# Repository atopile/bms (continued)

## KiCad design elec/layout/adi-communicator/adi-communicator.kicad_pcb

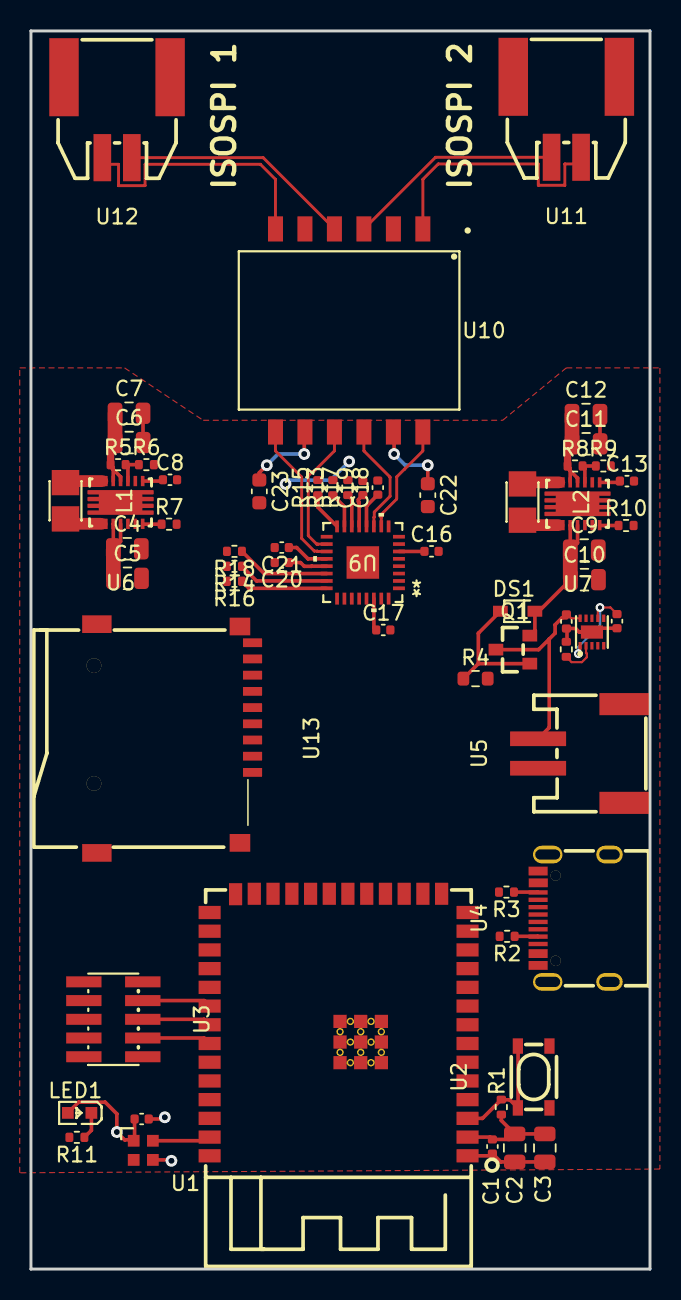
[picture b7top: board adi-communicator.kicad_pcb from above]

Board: 4 copper layers, 42.0 x 84.0 mm, 61 parts (0 on the bottom side), 53 nets.

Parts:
C1, C8, C13, C16, C17, C18, C19, C20, C21, C24: 16V 100nF X7R ±10% 0402 Multilayer Ceramic Capaci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; C0402
C2, C3, C4, C5, C6, C7, C9, C10, C11, C12: 25V 10uF X5R ±10% 0805 Multilayer Ceramic Capacit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; C0805
C14, C15: 25V 1uF X5R ±10% 0402 Multilayer Ceramic Capacito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; C0402
C22, C23: 50V 10nF X7R ±10% 0603 Multilayer Ceramic Capacit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; C0603
DS1: SOD-323_L1.8-W1.3-LS2.5-RD
L1, L2: IND-SMD_L2.5-W2.0_WPN252012H
LED1: LED0603-RD
Q1: SOT-23_L2.9-W1.3-P1.90-LS2.4-BR
R1: 62.5mW Thick Film Resistors 50V ±100ppm/℃ ±1% 10k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; R0402
R2, R3: 62.5mW Thick Film Resistors 50V ±100ppm/℃ ±1% 4.7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; R0402
R4: 100mW Thick Film Resistors 75V ±100ppm/℃ ±1% 10kΩ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; R0603
R5: 62.5mW Thick Film Resistors 50V ±100ppm/℃ ±1% 25.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; R0402
R6: 62.5mW Thick Film Resistors ±100ppm/℃ ±1% 2.8kΩ 0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; R0402
R7, R10: 62.5mW Thick Film Resistors 50V ±100ppm/℃ ±1% 1MΩ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; R0402
R8: 62.5mW Thick Film Resistors 50V ±100ppm/℃ ±1% 23.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; R0402
R9: 62.5mW Thick Film Resistors 50V ±100ppm/℃ ±1% 4.3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; R0402
R11: 62.5mW Thick Film Resistors 50V ±100ppm/℃ ±1% 330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; R0402
R12: 62.5mW Thick Film Resistors 75V ±1% ±100ppm/℃ 576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; R0402
R13, R14, R15, R16, R17, R18: 0Ω; R0402
U1: WIRELM-SMD_ESP32-S3-WROOM-1
U2: KEY-SMD_4P-L4.2-W3.2-P2.20-LS4.6
U3: HDR-SMD_10P-P1.27-V-M-R2-C5-LS5.3
U4: USB-C-SMD_KH-TYPE-C-16P
U5: CONN-SMD_P2.00_S2B-PH-SM4-TB-LF-SN
U6, U7: VSON-14_L4.0-W3.0-P0.50-BL-EP_TI_DSJ
U8: WSON-10_L2.0-W2.0-P0.40-BL-EP
U9: 05-08-7057_ADI
U10: SMD-12_L14.8-W11.7-P2.00-LS14.7
U11, U12: CONN-SMD_2P-P2.00_MOLEX_5023520201
U13: TF-SMD_TF-01A
U14: LED-SMD_4P-L2.0-W2.0-BR

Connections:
_3v3_reg.feedback_div-out: R8.2, R9.1, U7.3
_3v3_reg.ic-l1: L2.1, U7.8, U7.9
_3v3_reg.ic-l2: L2.2, U7.6, U7.7
_3v3_reg.ic-pg: R10.1, U7.14
_3v3_reg.ic-vina: C13.1, U7.1, U7.12
_5v_reg-vcc: C6.1, C7.1, C18.1, C19.1, C20.1, C21.1, R5.1, U6.4, U6.5, U9.12, U9.13, U9.20, U9.21
_5v_reg.feedback_div-out: R5.2, R6.1, U6.3
_5v_reg.ic-l1: L1.1, U6.8, U6.9
_5v_reg.ic-l2: L1.2, U6.6, U6.7
_5v_reg.ic-pg: R7.1, U6.14
_5v_reg.ic-vina: C8.1, U6.1, U6.12
battery_conn-vcc: C15.1, Q1.3, U5.2, U8.10
cathode: LED1.1, R11.1
cc1: R2.1, U4.A5
cc2: R3.1, U4.B5
cs: U1.18, U13.2
dm: U1.13, U4.A7, U4.B7
dp: U1.14, U4.A6, U4.B6
en: R1.2, U1.3, U2.1, U2.2
io1: U1.39, U14.4
io8: U1.12, U9.5
io18: U1.11, U9.29
iset: R12.1, U8.2
isospi_hv_1+: U10.3, U11.1
isospi_hv_1-: U10.1, U11.2
isospi_hv_2+: U10.6, U12.1
isospi_hv_2-: U10.4, U12.2
isospi_safe_1+: U9.11, U10.10
isospi_safe_1-: U9.10, U10.12
isospi_safe_2+: U9.19, U10.7
isospi_safe_2-: U9.18, U10.9
logic_1_center: C22.1, U10.11
logic_2_center: C23.1, U10.8
phapol: R17.1, U9.14
phapol2: R18.1, U9.22
power_prio-vcc: C4.1, C5.1, C9.1, C10.1, DS1.1, Q1.2, U6.10, U6.11, U7.10, U7.11
rto: R13.1, U9.15
rto2: R14.1, U9.23
tck: U1.32, U3.4
tdi: U1.34, U3.8
tdo: U1.33, U3.6
tms: U1.35, U3.2
uc.ic-gnd: C1.2, C2.2, C3.2, C4.2, C5.2, C6.2, C7.2, C8.2, C9.2, C10.2, C11.2, C12.2, C13.2, C14.2, C15.2, C16.2, C17.2, C18.2, C19.2, C20.2, C21.2, C22.2, C23.2, C24.2, R2.2, R3.2, R4.2, R6.2, R7.2, R9.2, R10.2, R11.2, R12.2, R13.2, R14.2, R15.2, R16.2, R17.2, R18.2, U1.1, U1.40, U1.41, U2.3, U2.4, U3.3, U3.5, U3.9, U4.1, U4.2, U4.3, U4.4, U4.A1, U4.A12, U4.B1, U4.B12, U5.1, U6.2, U6.13, U6.15, U7.2, U7.13, U7.15, U8.3, U8.11, U9.9, U9.17, U9.33, U13.6, U13.10, U13.11, U13.12, U13.13, U14.3
uc.ic-miso: U1.21, U13.7
uc.ic-miso-1: U1.16, U9.3, U9.27
uc.ic-mosi: U1.19, U13.3
uc.ic-mosi-1: U1.17, U9.2, U9.26
uc.ic-sck: U1.20, U13.5
uc.ic-sck-1: U1.15, U9.4, U9.28
uc.ic-vcc: C1.1, C2.1, C3.1, C11.1, C12.1, C16.1, C17.1, C24.1, LED1.2, R1.1, R8.1, U1.2, U3.1, U7.4, U7.5, U9.6, U9.30, U13.4, U14.1
usb_conn-vcc: C14.1, DS1.2, Q1.1, R4.1, U4.A4, U4.A9, U4.B4, U4.B9, U8.1, U8.7
xcvrmd: R15.1, U9.16
xcvrmd2: R16.1, U9.24

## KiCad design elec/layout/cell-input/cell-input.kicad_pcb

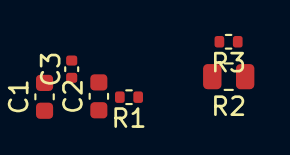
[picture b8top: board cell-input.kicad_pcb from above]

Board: 2 copper layers, 6 parts (0 on the bottom side), 4 nets, no tracks yet.

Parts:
C1: 50V 10nF X7R ±10% 0603 Multilayer Ceramic Capacit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; C0603
C2: 50V 100nF X7R ±10% 0603 Multilayer Ceramic Capaci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; C0603
C3: 16V 100nF X7R ±10% 0402 Multilayer Ceramic Capaci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; C0402
R1: 62.5mW Thick Film Resistors 50V ±100ppm/℃ ±1% 200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; R0402
R2: 125mW Thick Film Resistors 150V ±1% ±200ppm/℃ 20Ω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; R0805
R3: 62.5mW Thick Film Resistors 50V ±100ppm/℃ ±1% 1.6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; R0402

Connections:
n-2: C2.2, C3.1, R3.2
p: R1.1, R2.1
p-1: C1.1, R1.2
p-2: C2.1, R2.2

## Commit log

2024-07-02 Configure project
2024-07-03 initial design of ADBMS6830 dev board
2024-07-03 add isospi connector
2024-07-04 layout complete
2024-07-04 remove tabs from adi-communicator
2024-07-04 fix capitalization for rp2040 import
2024-07-05 added components for active cellsim + initial structure
2024-07-06 Add ESP32 for communicator
2024-07-06 Add ADBMS6822 IC + module
2024-07-06 Add isoloation transformer
2024-07-06 Add power architecture
2024-07-06 Schematic finished and building!
2024-07-06 Remove xmas tree from layout
2024-07-06 Flip around the transformer to detangle external connections
2024-07-06 Link dependencies
2024-07-06 Re-add LDO and RP2040
2024-07-06 Re-attach bypass caps
2024-07-06 Override net names and rearrange GPIO connections for easier routing
2024-07-06 Placement and zones done. Small routing largely complete
2024-07-06 Fix config resistor placement
2024-07-06 Add DRC exclusions for knowns clearance issues
2024-07-06 Layout communicator
2024-07-06 Fix reference to RP2040Kit in devboard
2024-07-07 single cell design + layout complete
2024-07-08 layout progress
2024-07-08 add reset pullup to i2c mux, add current limiting resistors to DMM connections, update layout
2024-07-08 remove bmb dev board from builds
2024-07-09 adding bringup fw
2024-07-17 reading cell voltages
2024-07-18 progress on write registers
2024-07-18 write data working
2024-07-19 cleanup
2024-07-19 read aux registers
2024-07-22 fw working
